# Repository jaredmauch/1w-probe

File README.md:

# 1w-probe
1wire probe code

This code collects data from the DS18B20 temperature sensors connected to
a raspberry pi and sends it to a carbon/graphite server for storage and
rendering.

It stores the data in a local sqlite3 backlog if it can't reach the server.
You can manually re-submit the data using the included temp2carbon.py

/boot/config.txt needs this:

dtoverlay=w1-gpio-pullup,gpiopin=4,extpullup=5,pullup=on

the mcp3204.py code reads from MCP3204 on the SPI.  The resistor values and VREF are all coded to make it easy to sense and send data to your server as well.

I uploaded the eagle schematic and gerber zip for the latest board that works so you can have them made at a place like pcb.ng, jlcpcb or macrofab.

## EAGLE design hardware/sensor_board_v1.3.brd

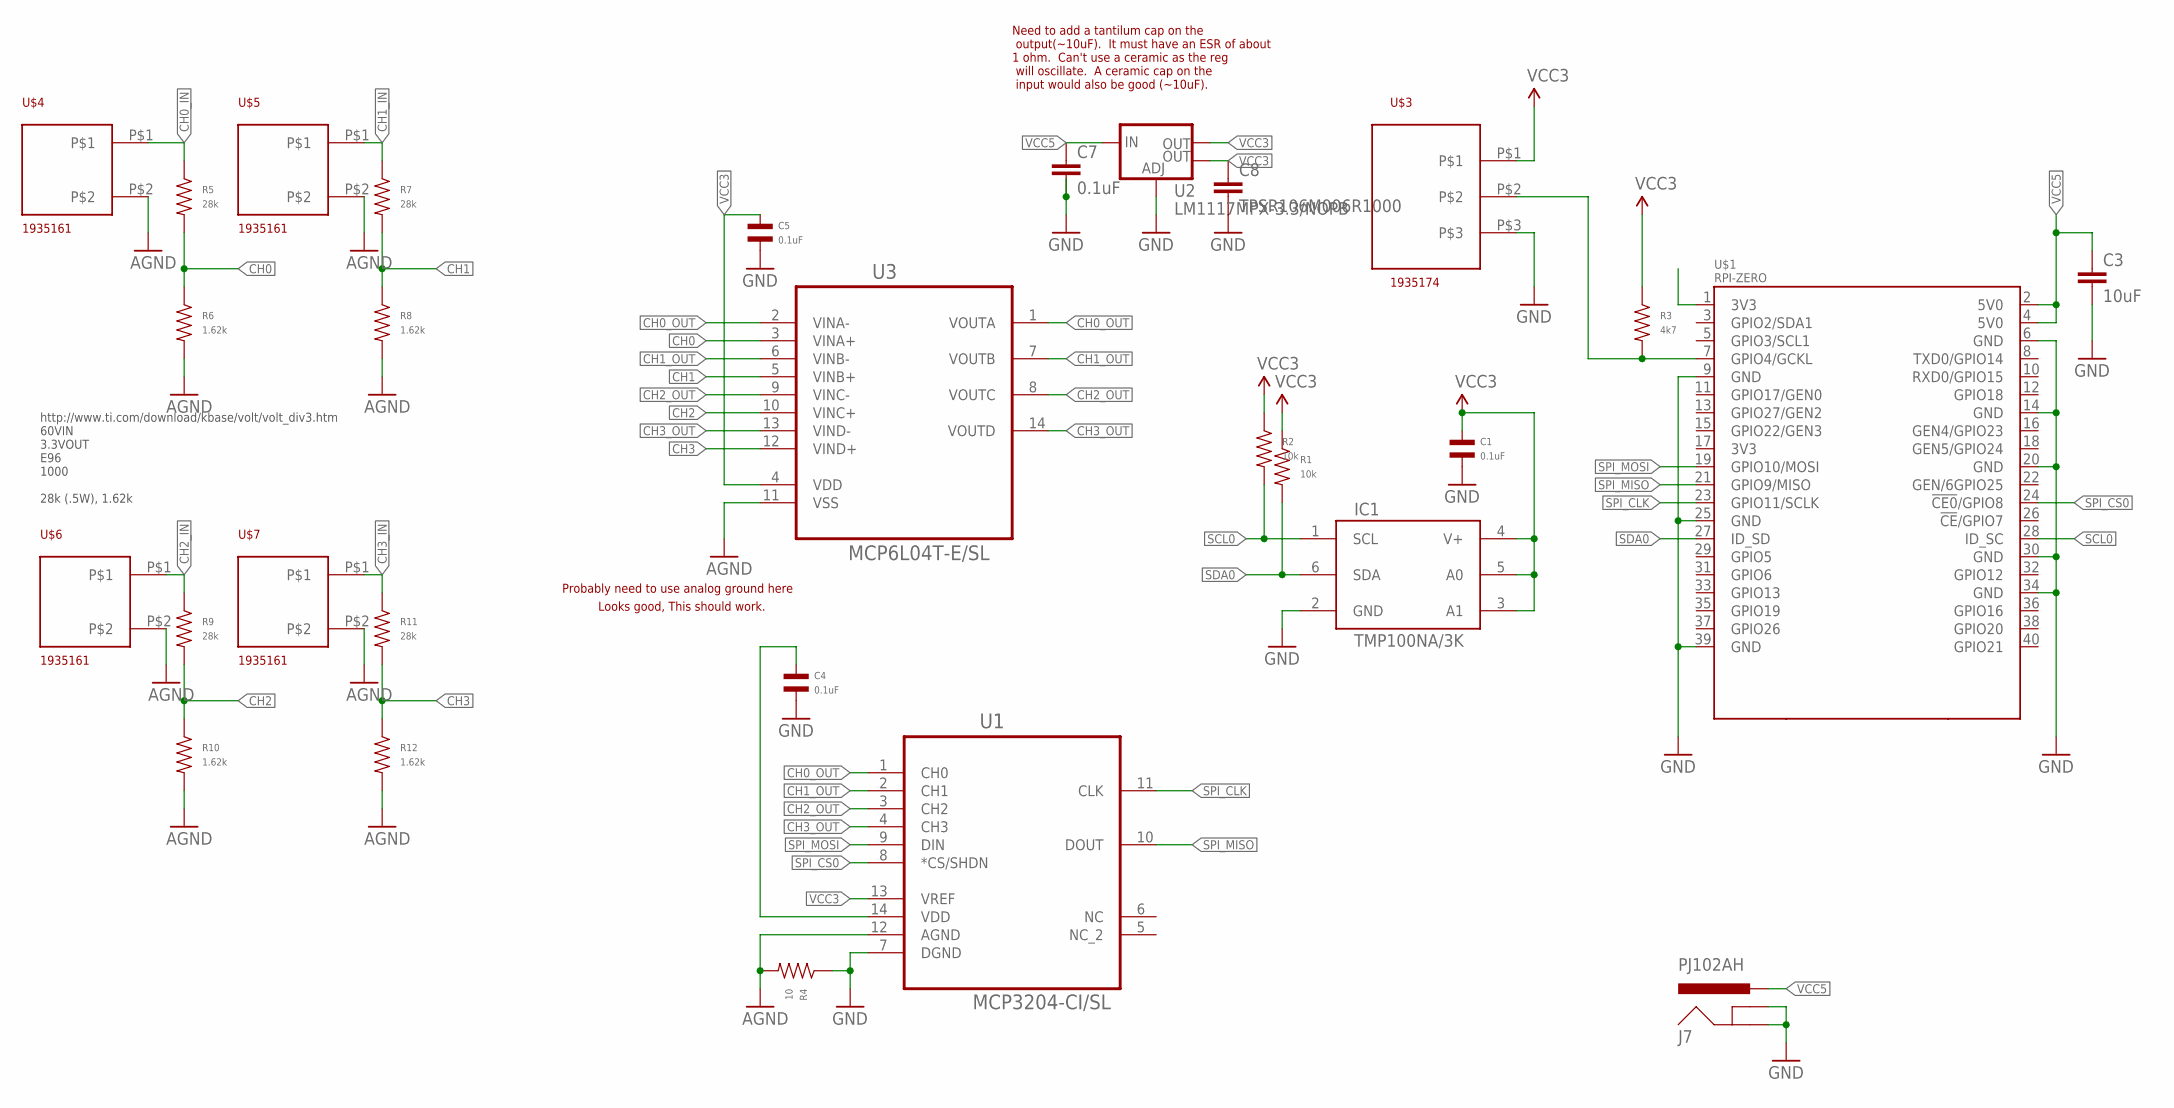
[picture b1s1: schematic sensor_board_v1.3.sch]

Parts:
C1, C4, C5: 0.1uF; C0603
C3: 10uF; 0603-CAP
C7: 0.1uF; 0603-CAP
C8: TPSR106M006R1000; 0805
IC1: TMP100NA/3K; TI-DBV
J7: PJ102AH; PJ-102AH
R1, R2: 10k; R0603
R3: 4k7; R0603
R4: 10; R1206
R5, R7, R9, R11: 28k; R1206; MPN RNCP1206FTD28K0
R6, R8, R10, R12: 1.62k; R1206
U1: MCP3204-CI/SL; SOIC127P600X175-14N
U2: LM1117MPX-3.3/NOPB; SOT223
U3: MCP6L04T-E/SL; SOIC127P600X175-14N
U$1: RPI-ZERO; RASPBERRYPI_BASTELSTUBE_V13_RASPI_BOARD_B+_FULL
U$3: 1935174
U$4, U$5, U$6, U$7: 1935161

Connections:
1WIRE_D: R3.P$2, U$1.7 (GPIO4/GCKL), U$3.P$2
AGND: R4.P$2, R6.P$2, R8.P$2, R10.P$2, R12.P$2, U1.12 (AGND), U3.11 (VSS), U$4.P$2, U$5.P$2, U$6.P$2, U$7.P$2
CH0: R5.P$2, R6.P$1, U3.3 (VINA+)
CH0_IN: R5.P$1, U$4.P$1
CH0_OUT: U1.1 (CH0), U3.1 (VOUTA), U3.2 (VINA-)
CH1: R7.P$2, R8.P$1, U3.5 (VINB+)
CH1_IN: R7.P$1, U$5.P$1
CH1_OUT: U1.2 (CH1), U3.6 (VINB-), U3.7 (VOUTB)
CH2: R9.P$2, R10.P$1, U3.10 (VINC+)
CH2_IN: R9.P$1, U$6.P$1
CH2_OUT: U1.3 (CH2), U3.8 (VOUTC), U3.9 (VINC-)
CH3: R11.P$2, R12.P$1, U3.12 (VIND+)
CH3_IN: R11.P$1, U$7.P$1
CH3_OUT: U1.4 (CH3), U3.13 (VIND-), U3.14 (VOUTD)
GND: C1.P$2, C3.2, C4.P$2, C5.P$2, C7.2, C8.2, IC1.2 (GND), J7.2 (GND), J7.3 (GNDBREAK), R4.P$1, U1.7 (DGND), U2.1 (ADJ), U$1.6 (GND), U$1.9 (GND), U$1.14 (GND), U$1.20 (GND), U$1.25 (GND), U$1.30 (GND), U$1.34 (GND), U$1.39 (GND), U$3.P$3
SCL0: IC1.1 (SCL), R2.P$2, U$1.28 (ID_SC)
SDA0: IC1.6 (SDA), R1.P$2, U$1.27 (ID_SD)
SPI_CLK: U1.11 (CLK), U$1.23 (GPIO11/SCLK)
SPI_CS0: U1.8 (*CS/SHDN), U$1.24 (!CE0!/GPIO8)
SPI_MISO: U1.10 (DOUT), U$1.21 (GPIO9/MISO)
SPI_MOSI: U1.9 (DIN), U$1.19 (GPIO10/MOSI)
VCC3: C1.P$1, C4.P$1, C5.P$1, C8.1, IC1.3 (A1), IC1.4 (V+), IC1.5 (A0), R1.P$1, R2.P$1, R3.P$1, U1.13 (VREF), U1.14 (VDD), U2.2 (OUT), U2.4 (OUT), U3.4 (VDD), U$1.1 (3V3), U$3.P$1
VCC5: C3.1, C7.1, J7.1 (PWR), U2.3 (IN), U$1.2 (5V0), U$1.4 (5V0)

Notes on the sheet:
Probably need to use analog ground here
Looks good, This should work.
http://www.ti.com/download/kbase/volt/volt_div3.htm 60VIN 3.3VOUT E96 1000 28k (.5W), 1.62k
Need to add a tantilum cap on the output(~10uF). It must have an ESR of about 1 ohm. Can't use a ceramic as the reg will oscillate. A ceramic cap on the input would also be good (~10uF).

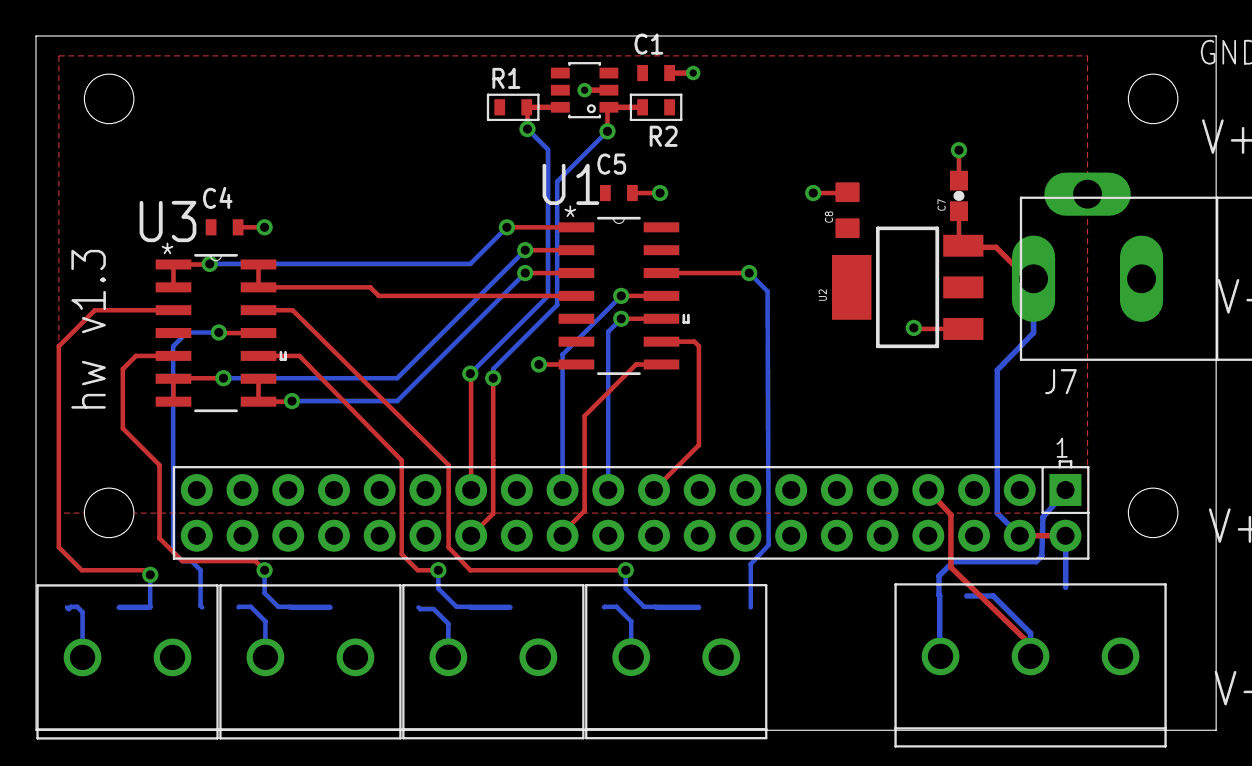
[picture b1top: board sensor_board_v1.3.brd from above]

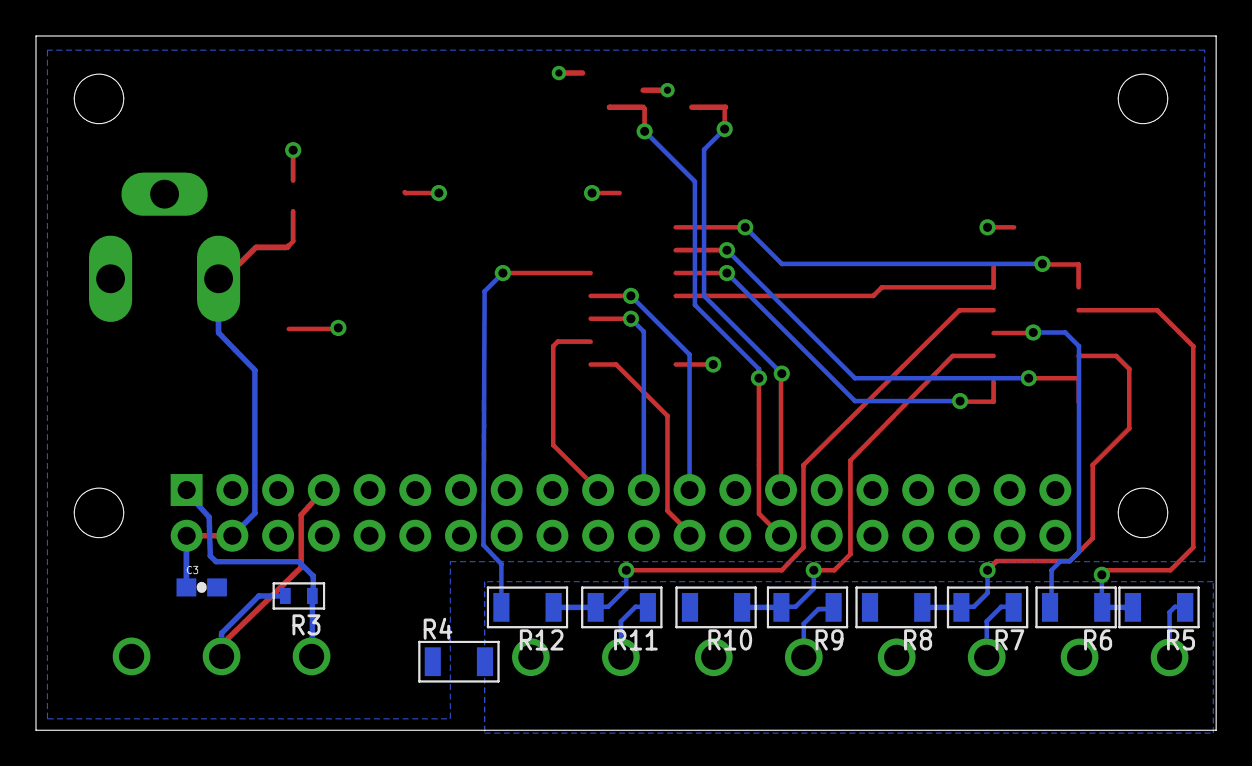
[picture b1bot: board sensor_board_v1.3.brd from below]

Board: 2 copper layers, 65.6 x 38.6 mm, 29 parts (11 on the bottom side), 23 nets.

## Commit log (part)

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2015-03-20 add files to repo
2015-03-21 improve tempdata.php generation add longer delay to tempsensor.py
2015-06-28 make code more robust
2016-04-29 update code
2016-05-13 push these in too
2016-05-14 tweak code
2016-09-22 prepare code for graphite/carbon store
2017-12-27 send data to carbon/graphite
2017-12-27 remove php
2017-12-27 update documentation
2017-12-27 add temp2carbon.py
2017-12-27 make code generic
2018-01-02 add some documentaiton
2019-11-27 add config
2019-11-27 add filename
2019-11-27 use yaml config
2019-11-28 python3 compatability fixes, move config to config.yaml, make streaming default, fallback to local sqlite3 as backup
2019-11-28 Resolve #1, #2
2020-01-19 pylint
2020-01-19 python3
2020-01-19 add hardware
2020-01-19 resolve #3 add sleep configuration option more pylint cleanup
2020-01-19 cleanup debug
2020-01-29 update files
2024-01-17 update Loader
2025-02-02 carbon -> influx1

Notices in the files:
parts and their libraries:
SparkFun-IC-Power: Licensing: Creative Commons ShareAlike 4.0 International - https://creativecommons.org/licenses/by-sa/4.0
